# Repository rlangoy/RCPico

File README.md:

# Raspbery Pi Pico W RC car
 WIFI RC Car controller using RPI Pico W <br>

The car can be controlled using an web-browser on a mobilephone or PC using  WIFI <br>

There is no need for a PCB, just connect the hardware compenents using wires acording to the [schematics](KicadV7#rp2040-pinout)

To cleanup the wires the project includes a PCB-boarddesign  for the 3D printed car [Gamma 2.0](https://cults3d.com/en/3d-model/gadget/gamma-2-demo) <br>

## Project Content 

### KicadV7  
PCB Design files for [Kicadv7](https://www.kicad.org/) \
&nbsp; More Hardware info is available in the [README](/KicadV7/README.md) 

# Software
The software is developed using [MicroPython](https://micropython.org/) \
&nbsp;  on a [Raspberry Pi Pico W](https://www.raspberrypi.com/products/raspberry-pi-pico/) <br>
&nbsp; More Info in the [README](/MicroPython/WifiController/README.md) 

## Instalation
### Firmware 
Download [RCPico.zip](https://github.com/rlangoy/RCPico/releases/download/v1.0/RCPico.zip) <br>

Unzip RCPico.zip <br>
 <br>
On the microcontroller, press the BOOTSEL button and hold it while you connect the USB cable to your computer <br>
&nbsp; A new drive would appear <br>
Copy the file RCPico.uf2 to the new drive <br>

## Conneting to the car
Scan the QRcode to connect to the car's wifi-network 

This conect you to the car-wifi with ssid = 'GemmmaRC#01' and password = '123456789'

Scann the QRcode to connect to the car's controller/joystock

Open the web-page 192.168.4.1 and now you are ready :)

# 3dr Party resources
## Hardware
For a harrdware list see the [Bil of materials](KicadV7#bil-of-materials-bom) :)

## Software compoenents
[microdot - Micropython web framework](https://github.com/miguelgrinberg/microdot) <br>
[nipplejs - JoyStick JavaScript](https://github.com/yoannmoinet/nipplejs)
## Software tools
[picotool](https://github.com/raspberrypi/picotool) used to grenerate the firmware-file (RCPico.u2f)  <br>
&nbsp; (picotool save -a -f RCPPico.uf2) <br>
# License

<br />This work is licensed under a <a rel="license" href="http://creativecommons.org/licenses/by/4.0/">Creative Commons Attribution 4.0 International License</a>.

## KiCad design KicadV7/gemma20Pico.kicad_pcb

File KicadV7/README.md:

# Kicad Files for the RCPico
### NB  Work in progress things might nor work widt selected components..
## PCB Layout. 

U2 DRV8833 motor controller needs to be soldered upside down as shown in the photo below 

## RP2040 Pinout 

## Connections

## Bil of Materials (BOM)
### PCB

| Quantity | Ref   | Prod no             | Description                 | URL                                                        |
|----------|-------|---------------------|-----------------------------|------------------------------------------------------------|
| 1        | U1    | Rasbperry Pi Pico W | Microcontroller with wifi   |  [Farnell](https://no.farnell.com/raspberry-pi/raspberry-pi-pico-w/raspberry-pi-board-arm-cortex/dp/3996082?ost=rasbperry+pi+pico+w&autoc=raspberry+pi+pico+w)   |
| 1        | U2    | 1005001633854429    | DRV8833 Motor Driver Module | [Aliexpress](https://www.aliexpress.com/item/1005001633854429.html)  |
| 2        | J1-J2 | 1005005522977746    | 6 pin socket 2.54mm         | [Aliexpress](https://www.aliexpress.com/item/1005005522977746.html)  |
| 1        | J3    | 1005004843759392    | 2 pin header 2.54mm         | [Aliexpress](https://www.aliexpress.com/item/1005004843759392.html)  |
| 1        | J4    | 32880456356         | Connector XH 2.0mm          | [Aliexpress](https://www.aliexpress.com/item/32880456356.html)       |
| 3        | J5-J7 | 1005005522977746    | 3 pin Socket 2.54mm         | [Aliexpress](https://www.aliexpress.com/item/1005005522977746.html)  |
| 1        | EXT1  | 1005004123467947    | 2x7 Header 2.54mm           | [Aliexpress](https://www.aliexpress.com/item/1005004123467947.html)  |
| 1        |  M1   |     | 130 DC Motor                |  |
| 1        |  M2   | 1005003137639801    | GH-S37D Servo               | [Aliexpress](https://www.aliexpress.com/item/1005003137639801.html)  |
| 1        |  BT1  | 1005001859207575    | 3.7V 400mAh Lipo            | [Aliexpress](https://www.aliexpress.com/item/1005001859207575.html)  |

Not recommended..  130 DC Motor 1005005481288051  [Aliexpress](https://www.aliexpress.com/item/1005005481288051.html) 
### Other Hardware 

| Quantity | Ref   | Prod no             | Description                  | URL                                                        |
|----------|--------|---------------------|-----------------------------|------------------------------------------------------------|
| 1        |  NA    | 1005001623293545    | 0.5M 8-Teeth Pinion 1.95mm    |  [Aliexpress](https://www.aliexpress.com/item/1005001623293545.html)   |
| 1        | PCB    | PCB00               | PCB Production files (gerber) |  [Gerber files](https://github.com/rlangoy/RCPico/raw/main/KicadV7/gerber/gemma20Pico.zip "Gerber files")
| 1        | CAR    | GAMMA20             | PIP 3D printed Car            |  [Gamma 2.0](https://cults3d.com/en/3d-model/gadget/gamma-2-demo)     |

### Optional Hardware for autonomus steering

| Quantity | Ref   | Prod no             | Description                | URL                                                         |
|----------|-------|---------------------|-----------------------------|------------------------------------------------------------|
| 2        |  NA    | 32708290585        |  APDS-9900                  |  [Aliexpress](https://www.aliexpress.com/item/32708290585.html)       |

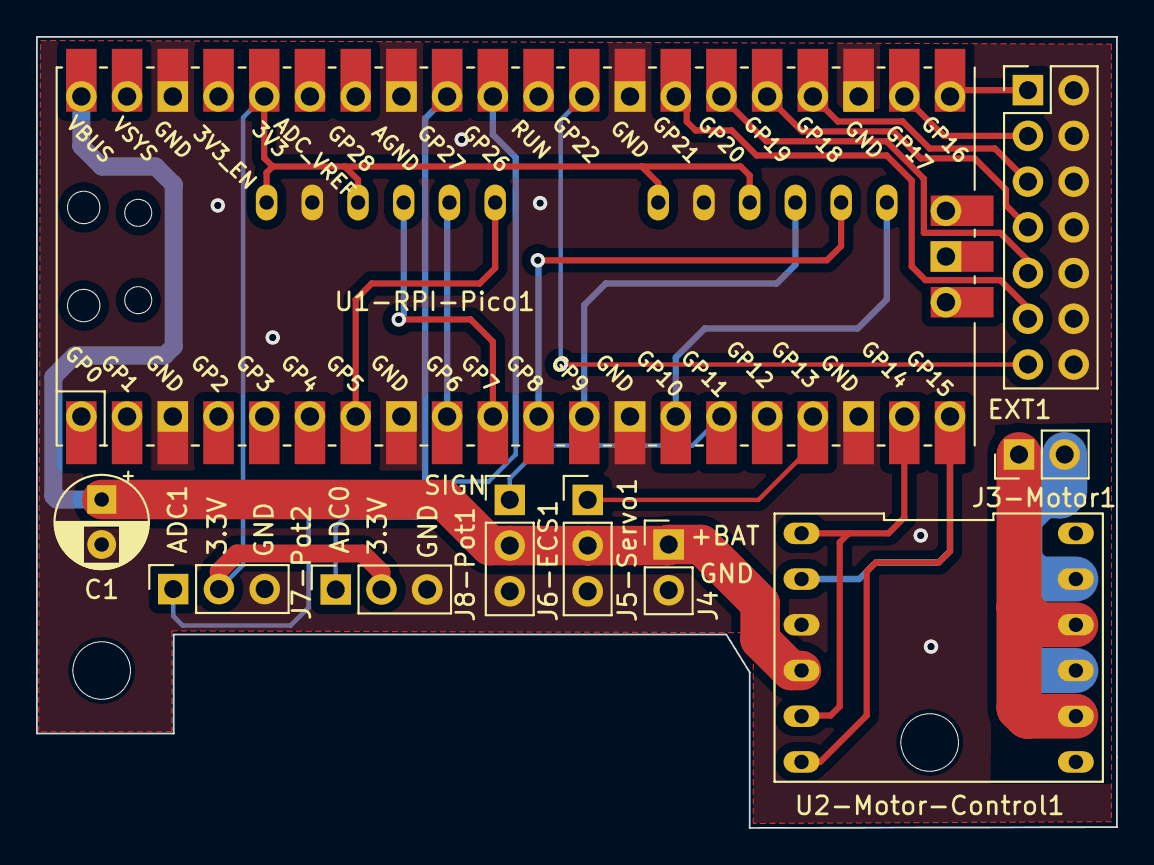
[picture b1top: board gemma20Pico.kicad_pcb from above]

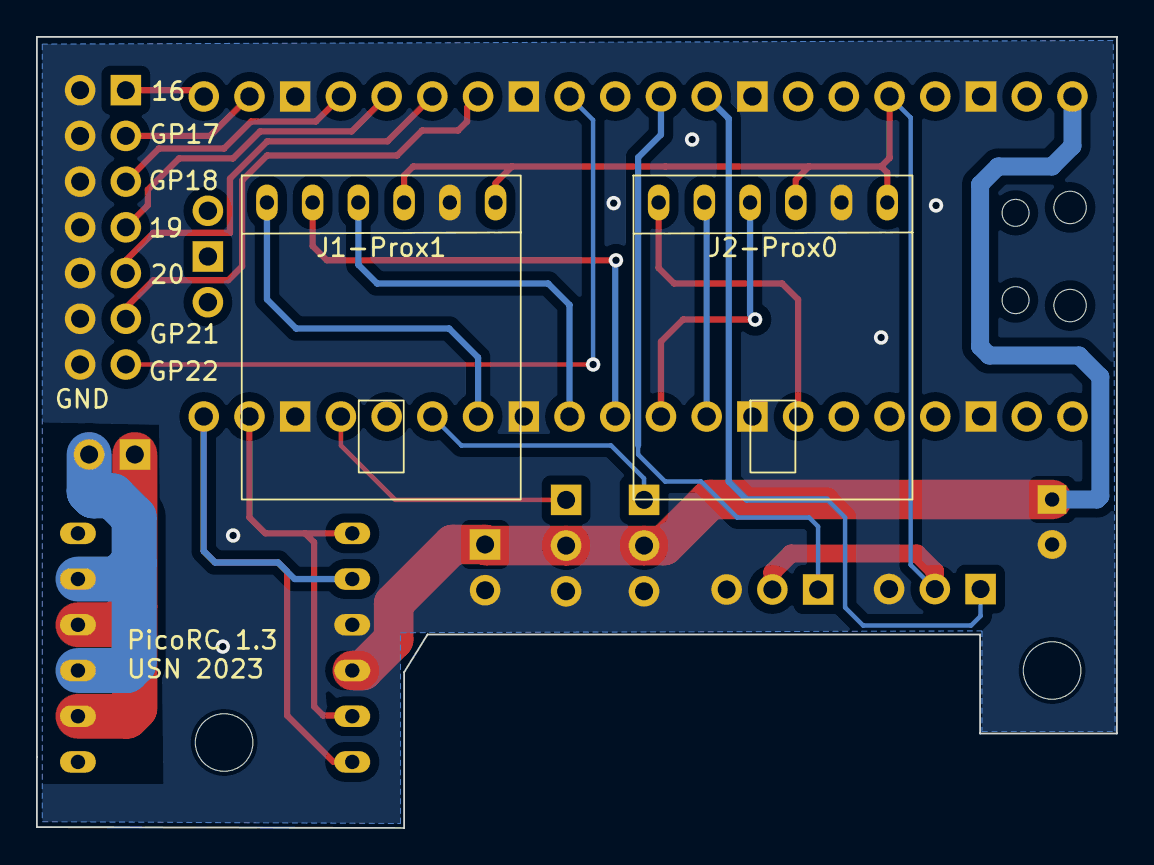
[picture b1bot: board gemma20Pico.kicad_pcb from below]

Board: 2 copper layers, 60.0 x 44.0 mm, 12 parts (2 on the bottom side), 24 nets.

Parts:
C1: C_Polarized_Small_US; CP_Radial_D5.0mm_P2.50mm
EXT1: Ext; PinHeader_2x07_P2.54mm_Vertical
J1-Prox1: I2C_CH0; SIP-6
J2-Prox0: I2C_CH1; SIP-6
J3-Motor1: DC-Motor; PinHeader_1x02_P2.54mm_Vertical
J4: 3.7V Battery; PinHeader_1x02_P2.54mm_Vertical
J5-Servo1: Servo; PinHeader_1x03_P2.54mm_Vertical
J6-ECS1: ECS/Servo; PinHeader_1x03_P2.54mm_Vertical
J7-Pot2, J8-Pot1: Pot; PinSocket_1x03_P2.54mm_Vertical
U1-RPI-Pico1: Pico; RPi_Pico_SMD_TH
U2-Motor-Control1: DIP-12_600_ELL

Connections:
+3.3V: J1-Prox1.4, J1-Prox1.6, J2-Prox0.4, J2-Prox0.6, J7-Pot2.2, J8-Pot1.2, U1-RPI-Pico1.36 (3V3)
+BATT: C1.1, J4.1, J5-Servo1.2, J6-ECS1.2, U1-RPI-Pico1.40 (VBUS), U2-Motor-Control1.4 (VCC)
/ADC0: J8-Pot1.1, U1-RPI-Pico1.31 (GPIO26_ADC0)
/ADC1: J7-Pot2.1, U1-RPI-Pico1.32 (GPIO27_ADC1)
/ECS_SIGN: J6-ECS1.1, U1-RPI-Pico1.15 (GPIO11)
/GP16: EXT1.1, U1-RPI-Pico1.21 (GPIO16)
/GP17: EXT1.3, U1-RPI-Pico1.22 (GPIO17)
/GP18: EXT1.5, U1-RPI-Pico1.24 (GPIO18)
/GP19: EXT1.7, U1-RPI-Pico1.25 (GPIO19)
/GP20: EXT1.9, U1-RPI-Pico1.26 (GPIO20)
/GP21: EXT1.11, U1-RPI-Pico1.27 (GPIO21)
/GP22: EXT1.13, U1-RPI-Pico1.29 (GPIO22)
/INT0: J1-Prox1.1, U1-RPI-Pico1.14 (GPIO10)
/INT1: J2-Prox0.1, U1-RPI-Pico1.7 (GPIO5)
/MC_1: U1-RPI-Pico1.20 (GPIO15), U2-Motor-Control1.2 (IN3), U2-Motor-Control1.6 (IN1)
/MC_2: U1-RPI-Pico1.19 (GPIO14), U2-Motor-Control1.1 (IN4), U2-Motor-Control1.5 (IN2)
/MO1: J3-Motor1.2, U2-Motor-Control1.9 (OUT3), U2-Motor-Control1.11 (OUT1)
/MO2: J3-Motor1.1, U2-Motor-Control1.8 (OUT4), U2-Motor-Control1.10 (OUT2)
/SCL0: J1-Prox1.3, U1-RPI-Pico1.12 (GPIO9)
/SCL1: J2-Prox0.3, U1-RPI-Pico1.10 (GPIO7)
/SDA0: J1-Prox1.2, U1-RPI-Pico1.11 (GPIO8)
/SDA1: J2-Prox0.2, U1-RPI-Pico1.9 (GPIO6)
/Servo_SIGN: J5-Servo1.1, U1-RPI-Pico1.17 (GPIO13)
GND: C1.2, EXT1.2, EXT1.4, EXT1.6, EXT1.8, EXT1.10, EXT1.12, EXT1.14, J1-Prox1.5, J2-Prox0.5, J4.2, J5-Servo1.3, J6-ECS1.3, J7-Pot2.3, J8-Pot1.3, U1-RPI-Pico1.3 (GND), U1-RPI-Pico1.8 (GND), U1-RPI-Pico1.13 (GND), U1-RPI-Pico1.18 (GND), U1-RPI-Pico1.23 (GND), U1-RPI-Pico1.28 (GND), U1-RPI-Pico1.33 (AGND), U1-RPI-Pico1.38 (GND), U2-Motor-Control1.3 (GND)

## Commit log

2023-07-02 Added QR codes for wifi-onnect
2023-07-03 Send x and y posiotions as JSON
2023-07-03 Update index.html
    Title changed to RC Pico Controller
2023-07-03 Controll montion and steering
2023-07-03 Fix reversed steering
2023-07-03 Cleanup connectors
2023-07-04 Added websocket quing
    if there is a websocket que send only the last msg the othes is droped
2023-07-04 Fix Quing
2023-07-05 Schema update
2023-07-05 Added External components to the schematics
2023-07-05 Production files
2023-07-05 Add reset when releasing joystick
2023-07-06 Firmware Release v1.0
2023-07-07 Clean up controller images
2023-07-08 Drv8833 in paralell
2023-07-09 Connect H bridges in paralell
    Connect H-Bridges in paralell for 2xcurrent, added mounting holes , reduced board size to allow G9 Servo mount moved and rotated POT for easyer access to +3.3V
2023-07-11 Calibrates servos for GH-S37D
2023-07-11 Servo pos reversed and reduce motor PWM speed to alow H-Bridge to work
2023-07-12 Addad title head info
2023-07-12 Cleanup
2023-07-12 Added decoupling capacitor for the Pico amd added description
2023-07-17 Added ECS Pins & cleanup
    Added ECS connector allows the DRV8833 to be replaced with brushless motor controller for RC (also provides +5v)
2023-08-02 Reduced Size to better fir the new gamma2.0
2023-08-15 Update picures to lastest
2023-08-24 Fix Footprit Pox sensors was not updated
2023-09-26 update servo calibration
    Small update
2023-10-06 Uses Captive portal for ease of connecting
    Redirect DNS request to the microcontroller to avoid specifying the web-site (http://192.168.4.1/)
2023-10-11 Load servo range variabls from config.json
2023-10-11 fix add lib os
2023-10-11 start DSN and webserver in same event loop
2024-05-23 Added BLE support
